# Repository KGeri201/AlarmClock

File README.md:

# Alarm Clock
An Open-Source, easy to build alarm clock.

## Description
To make sure, that I can be in time I wanted to buy a new alarm clock to have beside my smartphone.  
I wanted one which is reliable, not depending on wall power and I can set, manage multiple alarms easily.  
I searced through some sites, but I could not find any, which I liked.  
So I designed my own.  
I wanted to mimik the clock of a general smartphone and set alarms easily through a touchscreen.  
Because I use an ESP32 I also hope to be able to display some notifications through bluetooth and use other features of it in the future.   

## Hardware
### PCB
It is a nearly one sided PCB.   
Unfortunatelly I had to make some GND-connections to the second site to make the design some sort of clean.  

#### Partlist  
|Amount | Value | Designation
|-|-|-
| 1 | ESP32-WROOM-32 (ESP32) | ESP32 
| 1 | ER-TFTM032-3 | LCD 
| 1 | LD1117AS33TR (Voltage-Regulator) | IC1 
| 1 | SUMMER EPM 121 (buzzer) | SG1 
| 5 | 0,1µF | C1, C2, C4, C5, C6 
| 2 | 10µF | C3, C7 
| 4 | 10k | R1, R2, R3, R9 
| 1 | BC817 (NPN Transistor) | T1 
| 1 | Button | BTN 
| 3 | AAA Batteryholder | BT1, BT2, BT3  

As an optional accesory you can get a BME280 sensor module and connect it to the pinheader marked for it on the board.

### Case
It is an easy to print case.  
Probaly will make a new, improved version in the future.

## Pinout
|GPIO | Screen
|-|-
| 12 | MISO
| 13 | MOSI
| 14 | SCLK
| 15 | CS
| 2 | DC
| nc | RST
| 16 | T_SCL
| 27 | T_SDA

|GPIO | BME280
|-|-
|33|-
|25|-

|GPIO | Other
|-|-
|32| Button
|26| Speaker
|35| voltage divider

## Software
**W**ork **i**n **P**rogress

## Credits
[KGeri201](https://github.com/KGeri201)

Special thanks to [HimbeersaftLP](https://github.com/HimbeersaftLP) for the help.

## License
[Apache License 2.0](LICENSE)

## Project status
In development.

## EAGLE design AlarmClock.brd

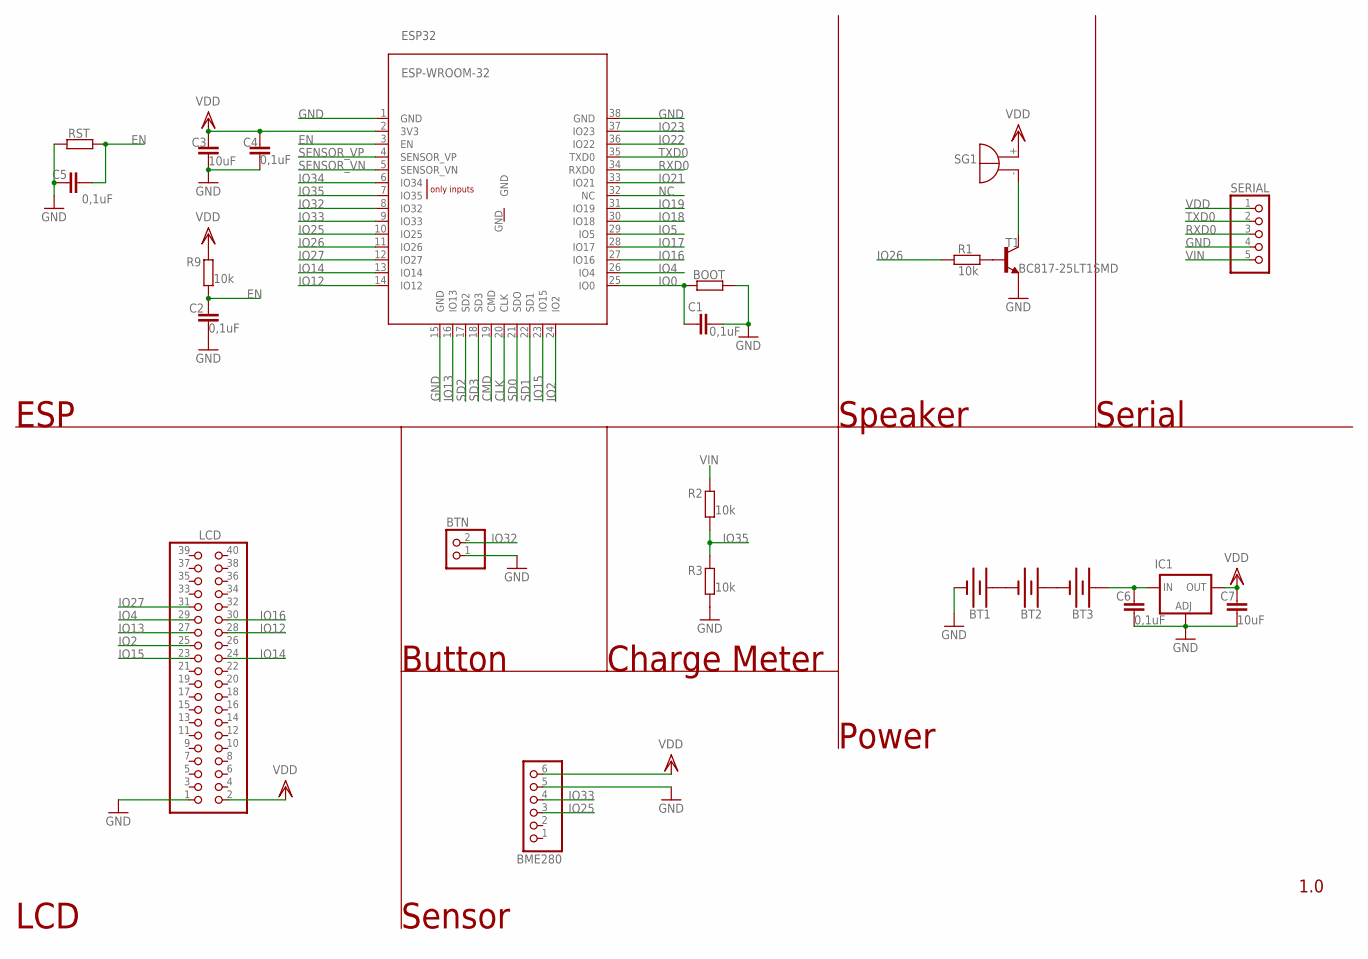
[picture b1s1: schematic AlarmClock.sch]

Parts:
BME280: PINHD-1X6; 1X06
BOOT: R-EU_R1206; R1206
BT1, BT2, BT3: HALTER1XUM4-LF
BTN: PINHD-1X2_2.54; 1X02
C1, C2, C4, C5, C6: 0,1uF; C1206
C3, C7: 10uF; C1206
ESP32: ESP-WROOM-32
IC1: LD1117AS33TR; SOT223
LCD: PINHD-2X20; 2X20
R1, R2, R3, R9: 10k; R1206
RST: R-EU_R1206; R1206
SERIAL: PINHD-1X5_2.54-SMD-90°; 1X05SMD/90
SG1: F/QMB
T1: BC817-25LT1SMD; SOT23-BEC

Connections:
CLK: ESP32.20 (CLK)
CMD: ESP32.19 (CMD)
EN: C2.2, C5.2, ESP32.3 (EN), R9.1, RST.2
GND: BME280.5, BOOT.2, BT1.P$2 (-), BTN.1, C1.1, C2.1, C3.1, C4.1, C5.1, C6.1, C7.1, ESP32.1 (GND), ESP32.15 (GND), ESP32.38 (GND), IC1.1 (ADJ), LCD.1, R3.1, RST.1, SERIAL.4, T1.E
IO0: BOOT.1, C1.2, ESP32.25 (IO0)
IO2: ESP32.24 (IO2), LCD.25
IO4: ESP32.26 (IO4), LCD.29
IO5: ESP32.29 (IO5)
IO12: ESP32.14 (IO12), LCD.28
IO13: ESP32.16 (IO13), LCD.27
IO14: ESP32.13 (IO14), LCD.24
IO15: ESP32.23 (IO15), LCD.23
IO16: ESP32.27 (IO16), LCD.30
IO17: ESP32.28 (IO17)
IO18: ESP32.30 (IO18)
IO19: ESP32.31 (IO19)
IO21: ESP32.33 (IO21)
IO22: ESP32.36 (IO22)
IO23: ESP32.37 (IO23)
IO25: BME280.3, ESP32.10 (IO25)
IO26: ESP32.11 (IO26), R1.1
IO27: ESP32.12 (IO27), LCD.31
IO32: BTN.2, ESP32.8 (IO32)
IO33: BME280.4, ESP32.9 (IO33)
IO34: ESP32.6 (IO34)
IO35: ESP32.7 (IO35), R2.1, R3.2
unnamed: SG1.- (+), T1.C
unnamed: BT1.P$1 (+), BT2.P$2 (-)
unnamed: BT2.P$1 (+), BT3.P$2 (-)
unnamed: R1.2, T1.B
NC: ESP32.32 (NC)
RXD0: ESP32.34 (RXD0), SERIAL.3
SD0: ESP32.21 (SDO)
SD1: ESP32.22 (SD1)
SD2: ESP32.17 (SD2)
SD3: ESP32.18 (SD3)
SENSOR_VN: ESP32.5 (SENSOR_VN)
SENSOR_VP: ESP32.4 (SENSOR_VP)
TXD0: ESP32.35 (TXD0), SERIAL.2
VDD: BME280.6, C3.2, C4.2, C7.2, ESP32.2 (3V3), IC1.4 (OUT), LCD.2, R9.2, SERIAL.1, SG1.+ (-)
VIN: BT3.P$1 (+), C6.2, IC1.3 (IN), R2.2, SERIAL.5

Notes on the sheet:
Power
1.0
ESP
LCD
Sensor
Button
Serial
Speaker
Charge Meter

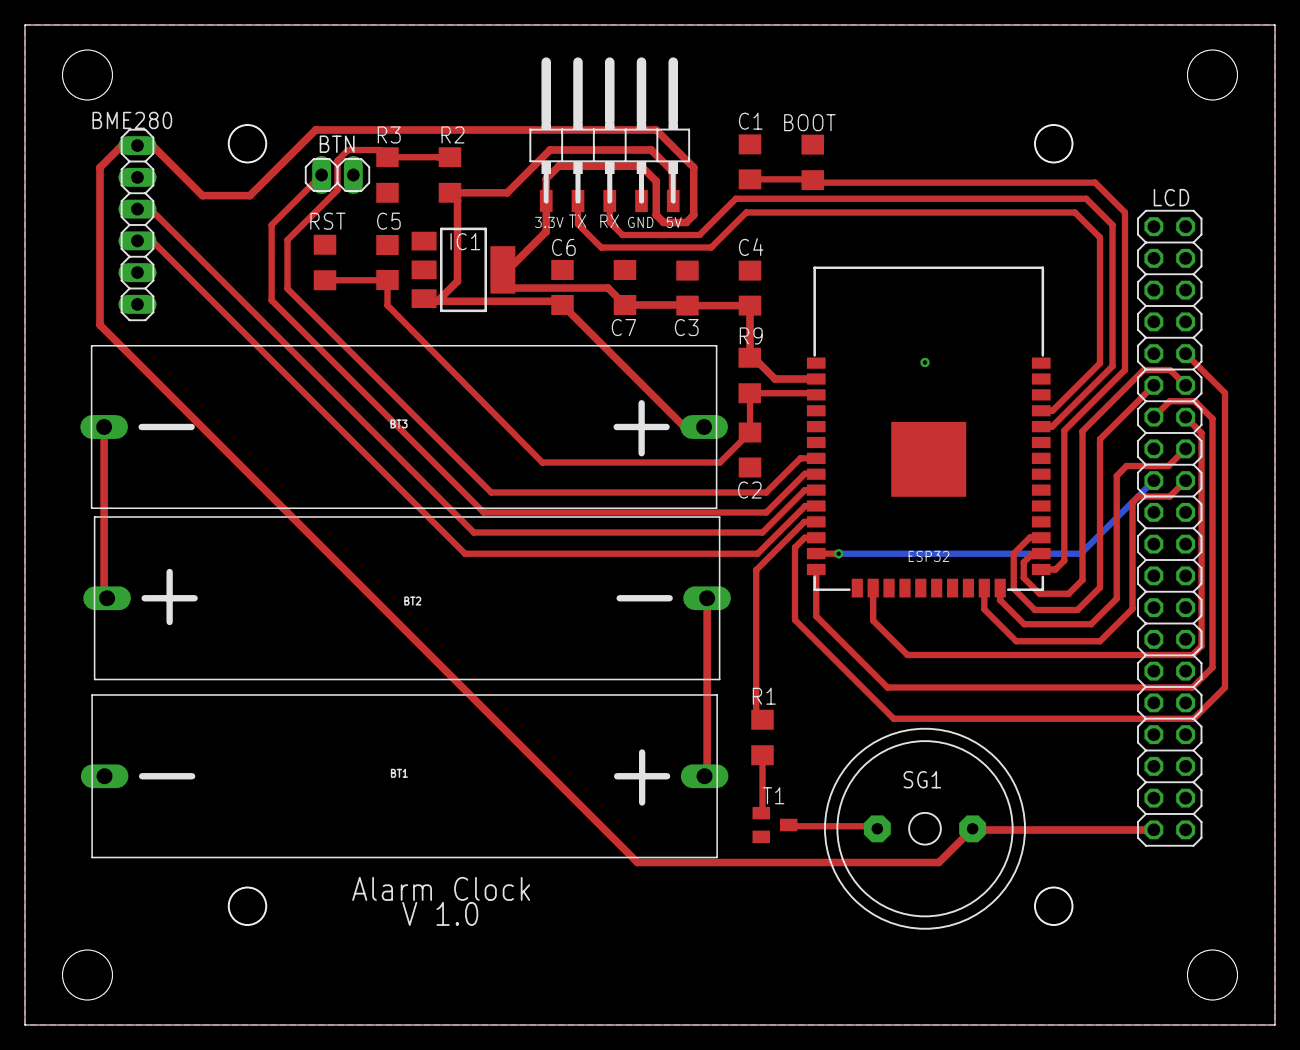
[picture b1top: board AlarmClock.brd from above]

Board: 2 copper layers, 99.8 x 79.8 mm, 24 parts (0 on the bottom side), 24 nets.

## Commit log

2022-01-02 added partlist
2022-08-17 Create LICENSE

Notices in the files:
parts and their libraries:
SparkFun-PowerSymbols: Licensing: Creative Commons ShareAlike 4.0 International - https://creativecommons.org/licenses/by-sa/4.0
